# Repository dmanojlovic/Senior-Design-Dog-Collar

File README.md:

# Senior-Design-Dog-Collar
Welcome to our github page for our senior design project, below is a brief explanation of what is in each folder. Learn more about our progress [here](https://engineering.purdue.edu/477grp5/)

## Hierarchy PCB
This folder contains our PCB schematic in an easy to read format
## PCB
This folder contains our footprints, schematic and symbols for our PCB design
## Server
This folder contains all the files running on the server including the data processing, UART communication and website hosting
## STM
This folder contains all the files needed for the STM32 chip that will be on the dog collar

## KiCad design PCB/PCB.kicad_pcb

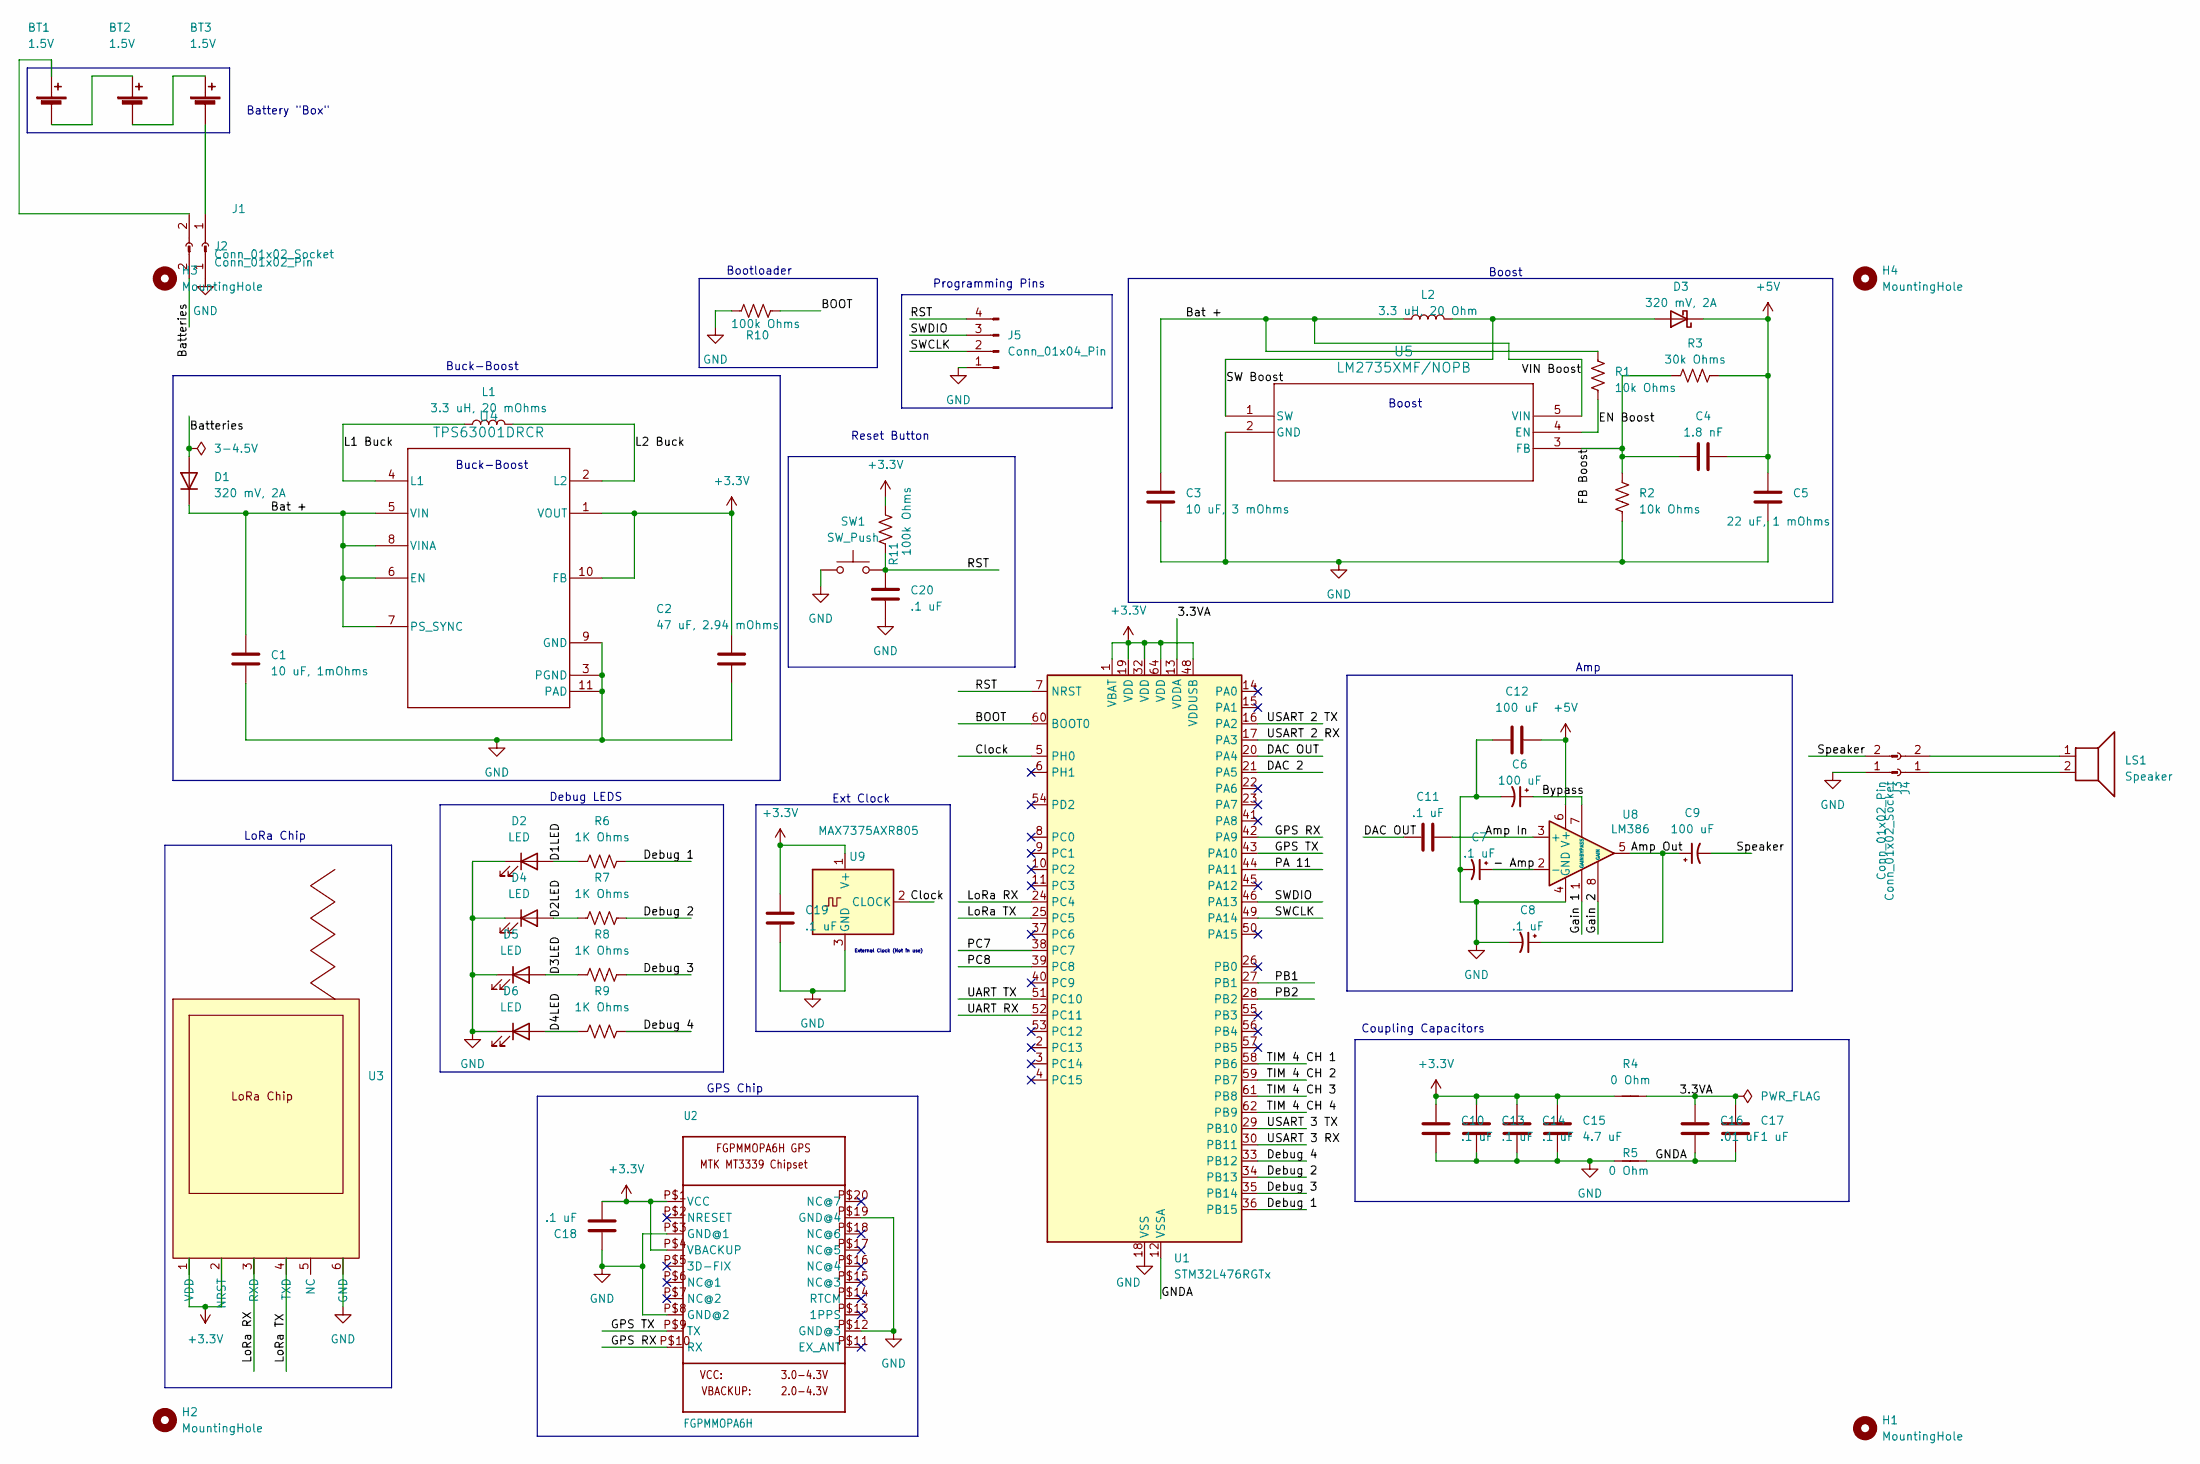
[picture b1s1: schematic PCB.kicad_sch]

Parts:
BT1, BT2, BT3: 1.5V
C1: 10 uF, 1mOhms; C_0805_2012Metric_Pad1.18x1.45mm_HandSolder
C2: 47 uF, 2.94 mOhms; C_0805_2012Metric_Pad1.18x1.45mm_HandSolder
C3: 10 uF, 3 mOhms; C_0805_2012Metric_Pad1.18x1.45mm_HandSolder
C4: 1.8 nF; C_0805_2012Metric_Pad1.18x1.45mm_HandSolder
C5: 22 uF, 1 mOhms; C_0805_2012Metric_Pad1.18x1.45mm_HandSolder
C6, C9: 100 uF; CAP_UZE_4X3P9_NCH
C7, C8: .1 uF; CAP_UZE_4X3P9_NCH
C10, C11, C13, C14, C18, C19, C20: .1 uF; C_0805_2012Metric_Pad1.18x1.45mm_HandSolder
C12: 100 uF; C_0805_2012Metric_Pad1.18x1.45mm_HandSolder
C15: 4.7 uF; C_0805_2012Metric_Pad1.18x1.45mm_HandSolder
C16: .01 uF; C_0805_2012Metric_Pad1.18x1.45mm_HandSolder
C17: 1 uF; C_0805_2012Metric_Pad1.18x1.45mm_HandSolder
D1, D3: 320 mV, 2A; Schottky
D2, D4, D5, D6: LED; LED_0805_2012Metric
H1, H2, H3, H4: MountingHole; MountingHole_2.1mm
J1, J4: Conn_01x02_Socket
J2, J3: Conn_01x02_Pin; JST_PH_B2B-PH-SM4-TB_1x02-1MP_P2.00mm_Vertical
J5: Conn_01x04_Pin; JST_EH_B4B-EH-A_1x04_P2.50mm_Vertical
L1: 3.3 uH, 20 mOhms; L_0805_2012Metric
L2: 3.3 uH, 20 Ohm; L_TDK_SLF7045
LS1: Speaker
R1, R2: 10k Ohms; R_0805_2012Metric_Pad1.20x1.40mm_HandSolder
R3: 30k Ohms; R_0805_2012Metric_Pad1.20x1.40mm_HandSolder
R4, R5: 0 Ohm; R_0805_2012Metric_Pad1.20x1.40mm_HandSolder
R6, R7, R8, R9: 1K Ohms; R_0805_2012Metric
R10, R11: 100k Ohms; R_0805_2012Metric
SW1: SW_Push; SW_PUSH_6mm_H5mm
U1: STM32L476RGTx; LQFP-64_10x10mm_P0.5mm
U2: FGPMMOPA6H
U3: LoRa Chip
U4: TPS63001DRCR; DRC0010J
U5: LM2735XMF/NOPB; MF05A
U8: LM386
U9: MAX7375AXR805; SOT-323_SC-70

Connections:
+3.3V: C2.1, C10.1, C13.1, C14.1, C15.1, C18.1, C19.1, R4.1, R11.2, U1.1 (VBAT), U1.19 (VDD), U1.32 (VDD), U1.48 (VDDUSB), U1.64 (VDD), U2.P$1 (VCC), U2.P$4 (VBACKUP), U3.1 (VDD), U3.2 (NRST), U4.1 (VOUT), U4.10 (FB), U9.1 (V+)
+5V: C4.2, C5.1, C12.1, D3.1 (K), R3.2, U8.6 (V+)
/3.3VA: C16.1, C17.1, R4.2, U1.13 (VDDA)
/- Amp: C7.1, U8.2 (-)
/Amp In: C11.2, U8.3 (+)
/Amp Out: C8.1, C9.1, U8.5
/BOOT: R10.2, U1.60 (BOOT0)
/Bat +: C1.1, C3.1, D1.1 (K), L2.1, R1.1, U4.5 (VIN), U4.6 (EN), U4.7 (PS_SYNC), U4.8 (VINA), U5.5 (VIN)
/Batteries: D1.2 (A), J2.2
/Bypass: C6.1, U8.7 (BYPASS)
/Clock: U1.5 (PH0), U9.2 (CLOCK)
/D1LED: D2.2 (A), R6.1
/D2LED: D4.2 (A), R7.1
/D3LED: D5.2 (A), R8.1
/D4LED: D6.2 (A), R9.1
/DAC 2: U1.21 (PA5)
/DAC OUT: C11.1, U1.20 (PA4)
/Debug 1: R6.2, U1.36 (PB15)
/Debug 2: R7.2, U1.34 (PB13)
/Debug 3: R8.2, U1.35 (PB14)
/Debug 4: R9.2, U1.33 (PB12)
/EN Boost: R1.2, U5.4 (EN)
/FB Boost: C4.1, R2.1, R3.1, U5.3 (FB)
/GNDA: C16.2, C17.2, R5.2, U1.12 (VSSA)
/GPS RX: U1.42 (PA9), U2.P$10 (RX)
/GPS TX: U1.43 (PA10), U2.P$9 (TX)
/Gain 1: U8.1 (GAIN)
/Gain 2: U8.8 (GAIN)
/L1 Buck: L1.1, U4.4 (L1)
/L2 Buck: L1.2, U4.2 (L2)
/LoRa RX: U1.24 (PC4), U3.3 (RXD)
/LoRa TX: U1.25 (PC5), U3.4 (TXD)
/PA 11: U1.44 (PA11)
/PB1: U1.27 (PB1)
/PB2: U1.28 (PB2)
/PC7: U1.38 (PC7)
/PC8: U1.39 (PC8)
/RST: C20.1, J5.4, R11.1, SW1.2, U1.7 (NRST)
/SW Boost: D3.2 (A), L2.2, U5.1 (SW)
/SWCLK: J5.2, U1.49 (PA14)
/SWDIO: J5.3, U1.46 (PA13)
/Speaker: C9.2, J3.2
/TIM 4 CH 1: U1.58 (PB6)
/TIM 4 CH 2: U1.59 (PB7)
/TIM 4 CH 3: U1.61 (PB8)
/TIM 4 CH 4: U1.62 (PB9)
/UART RX: U1.52 (PC11)
/UART TX: U1.51 (PC10)
/USART 2 RX: U1.17 (PA3)
/USART 2 TX: U1.16 (PA2)
/USART 3 RX: U1.30 (PB11)
/USART 3 TX: U1.29 (PB10)
GND: C1.2, C2.2, C3.2, C5.2, C6.2, C7.2, C8.2, C10.2, C12.2, C13.2, C14.2, C15.2, C18.2, C19.2, C20.2, D2.1 (K), D4.1 (K), D5.1 (K), D6.1 (K), J2.1, J3.1, J5.1, R2.2, R5.1, R10.1, SW1.1, U1.18 (VSS), U1.31 (VSS), U1.47 (VSS), U1.63 (VSS), U2.P$3 (GND@1), U2.P$8 (GND@2), U2.P$12 (GND@3), U2.P$19 (GND@4), U3.6 (GND), U4.3 (PGND), U4.9 (GND), U4.11 (PAD), U5.2 (GND), U8.4 (GND), U9.3 (GND)
unnamed: BT1.1 (+), J1.2
unnamed: BT1.2 (-), BT2.1 (+)
unnamed: BT2.2 (-), BT3.1 (+)
unnamed: BT3.2 (-), J1.1
unnamed: J4.1, LS1.2
unnamed: J4.2, LS1.1

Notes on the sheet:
Debug LEDS
External Clock (Not in use)
Programming Pins
Buck-Boost
Boost
Bootloader
LoRa Chip
Battery "Box"
GPS Chip
Boost
Amp
Reset Button
Coupling Capacitors
Ext Clock

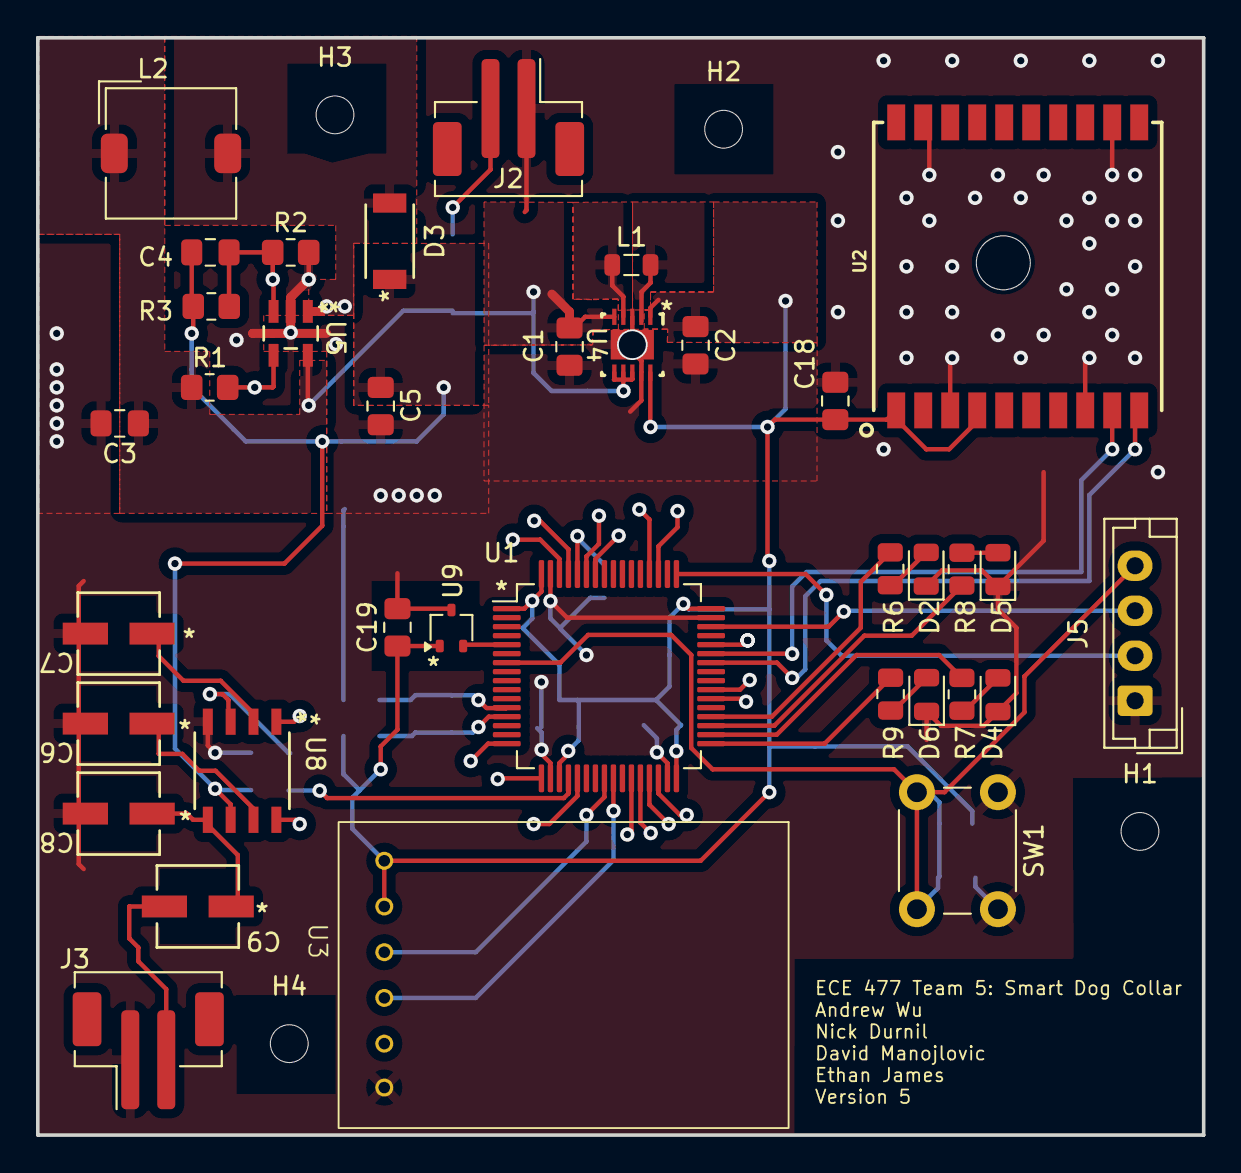
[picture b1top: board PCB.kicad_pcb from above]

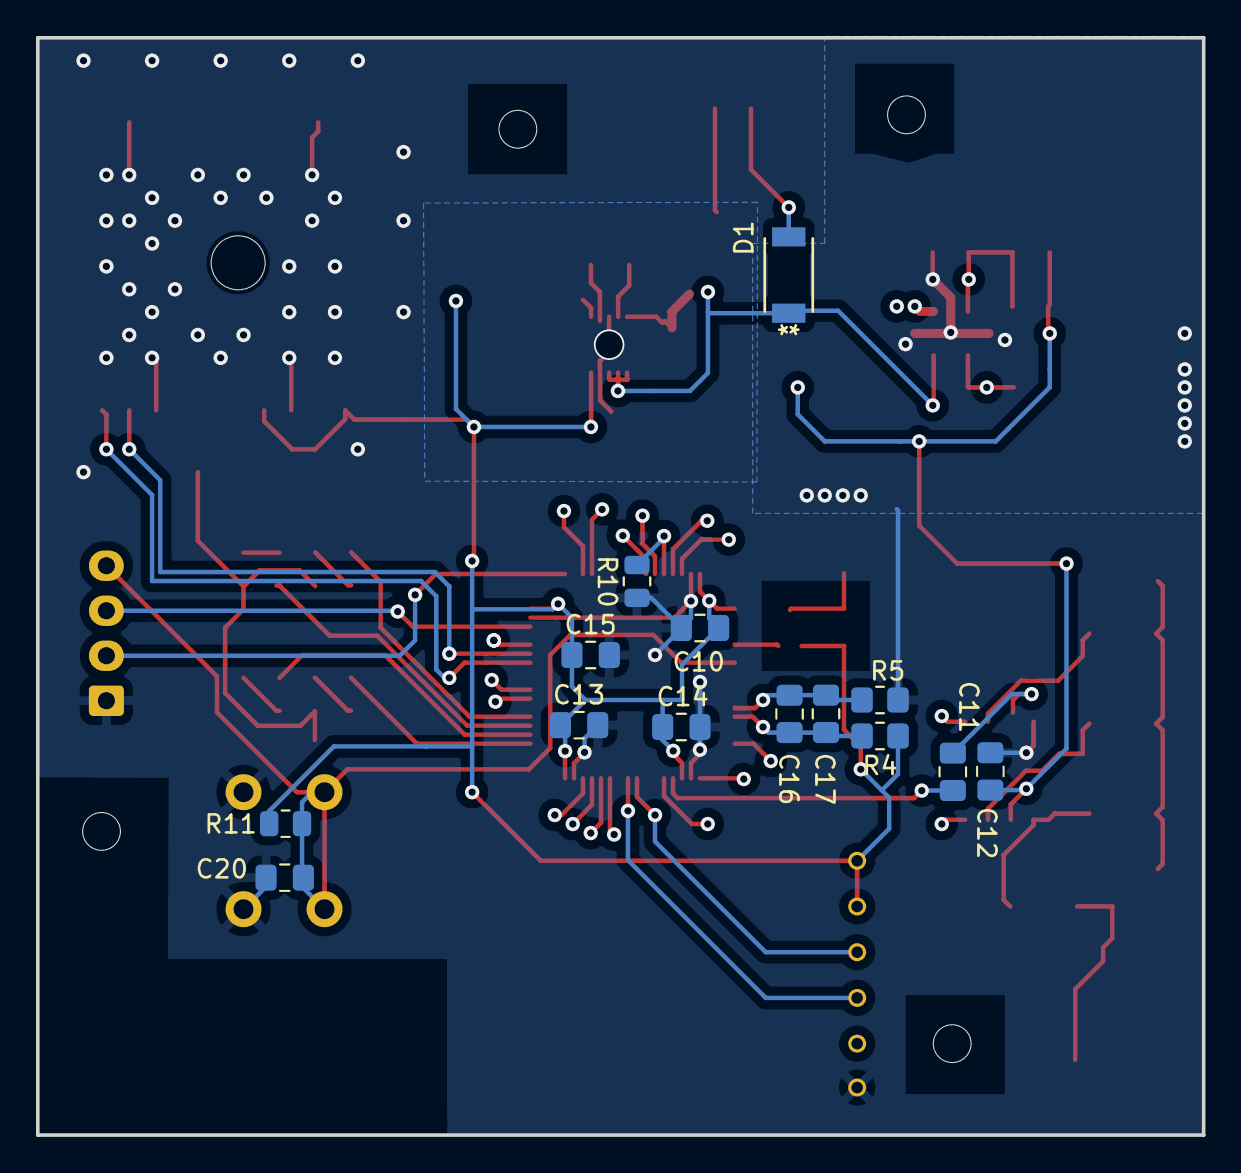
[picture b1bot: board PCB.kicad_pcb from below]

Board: 2 copper layers, 64.8 x 61.0 mm, 54 parts (14 on the bottom side), 35 nets.

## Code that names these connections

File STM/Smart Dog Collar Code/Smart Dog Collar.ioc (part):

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Mcu.Name=STM32L476R(C-E-G)Tx
Mcu.Package=LQFP64
Mcu.UserName=STM32L476RGTx
PA10.Mode=Asynchronous
PA10.Signal=USART1_RX
PA13\ (JTMS-SWDIO).Signal=SYS_JTMS-SWDIO
PA14\ (JTCK-SWCLK).Signal=SYS_JTCK-SWCLK
PA2.Mode=Asynchronous
PA2.Signal=USART2_TX
PA3.Mode=Asynchronous
PA3.Signal=USART2_RX
PA4.Signal=COMP_DAC11_group
PA9.Mode=Asynchronous
PA9.Signal=USART1_TX
PB12.Signal=GPIO_Output
PB13.Signal=GPIO_Output
PB14.Signal=GPIO_Output
PB15.Signal=GPIO_Output
PC13.Signal=GPIO_Input
PC3.Signal=GPXTI3
PC4.Signal=USART3_TX
PC5.Signal=USART3_RX
PH0-OSC_IN\ (PH0).Signal=RCC_OSC_IN
RCC.HSE_VALUE=8000000
RCC.SYSCLKFreq_VALUE=40000000
RCC.SYSCLKSource=RCC_SYSCLKSOURCE_PLLCLK
board=custom

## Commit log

2024-09-03 initial push
2024-09-03 Update UART.py
    I altered the port location to reflect the actual port configured for UART.
2024-09-04 website and uart commit
2024-09-05 init commit
2024-09-05 changes for mobile
2024-09-05 double text fix
2024-09-11 Added geofence data
2024-09-17 adding stm32 code
2024-10-01 Add files via upload
    KiCad files for the PCB schematic
2024-10-01 PCB desingn
    I added the files with the updated pages where someone will need to recreate each connection within the pages. The untitled schematic represents the Lora Chip which I forgot to change the name.
2024-10-02 Updated the indivdual components.
    Some of the individual components still need to be updated and completed. With the battery box, include the diode. The full schematic is not the update one as Andrew has the updated one with the corr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
2024-10-02 Add files via upload
    Finished everything except for the micro schematic
2024-10-02 Add files via upload
    Finished the main schematic as well as the sub schematics
2024-10-03 removed battery life
2024-10-03 cleaned up
2024-10-03 ignoring data and geofence json
2024-10-03 moved into folder
2024-10-03 website link added
2024-10-03 Add files via upload
    "Completed" schematic and started layout
2024-10-03 Add files via upload
    Updated footprints
2024-10-03 Add files via upload
    Reuploading due to saving error
2024-10-09 Add files via upload
    Need to decide how big the ground plane is, where to place the GPS, and connect the LoRa and GPS traces.
    Also need to add silkscreen layer and make sure checks in PCB verification checklist are completed.
2024-10-09 changed pcb
2024-10-09 Added a few things for presentation purposes
2024-10-09 Formatting on the Overall schematic
2024-10-09 Few more formatting things
2024-10-09 Updated Micro in hieracrchy
2024-10-09 updated micro hierarachy slightly
2024-10-09 Minor changes
2024-10-09 Changed name from unitled to lora so its more clear
2024-10-09 3d model fix
2024-10-10 pcb changes
2024-10-11 Schematic cleaned up
2024-10-11 pcb fix
2024-10-11 minor pcb changes
2024-10-11 minor pcb tweaks
2024-10-11 Add files via upload
    Finished PCB, awaiting check from professor and TAs
2024-10-16 Exlusion Zones added
2024-10-16 DRC Error fixes
2024-10-16 Debug vias added
2024-10-16 silkscreen visibility fix
2024-10-16 tweaks based on email
2024-10-16 version change on silk screan
2024-10-17 run python script on button call
2024-10-17 pcb v5
2024-10-17 gbr files
2024-10-17 closed pages
2024-10-17 gbr file fixes
2024-10-17 untented vias
2024-10-23 updated stm code. Includes GPS interrupt, LoRa send/receive, and play audio
2024-10-30 Integrated code
2024-11-01 3d model fixed
2024-11-01 tolerance fix
2024-11-04 python server setup and small website modifications
2024-11-14 Server Demo
2024-11-15 Working after resoldering microcontroller
2024-12-03 Updated interrupt code for Spark Challenge (after demo code)
